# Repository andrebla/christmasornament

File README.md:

# Christmas ornament

Christmas tree ornament for 2020 JLCPCB Design Challenge based in christmas PNG Designed By Co illustrasi from <a href="https://pngtree.com/">Pngtree.com</a>

It is a simple ornament using less than ten components, listed above:
## Bill of Materials ##
| # | Qty | Description |
| - | --- | :---------- | 
| 1 | 3 | 5mm red LED |
| 2 | 3 | 220 ohm 0603 resistor |
| 3 | 1 | smd 12mm battery holder |
| 4 | 1 | cr1220 battery |

It's simple and easy to build!

For more informaion about PCB fabrication visit JLCPCB - <a href="https://jlcpcb.com/">jlcpcb.com</a>

## 3D Render ##
|  | 
| - |

|  |
| - |

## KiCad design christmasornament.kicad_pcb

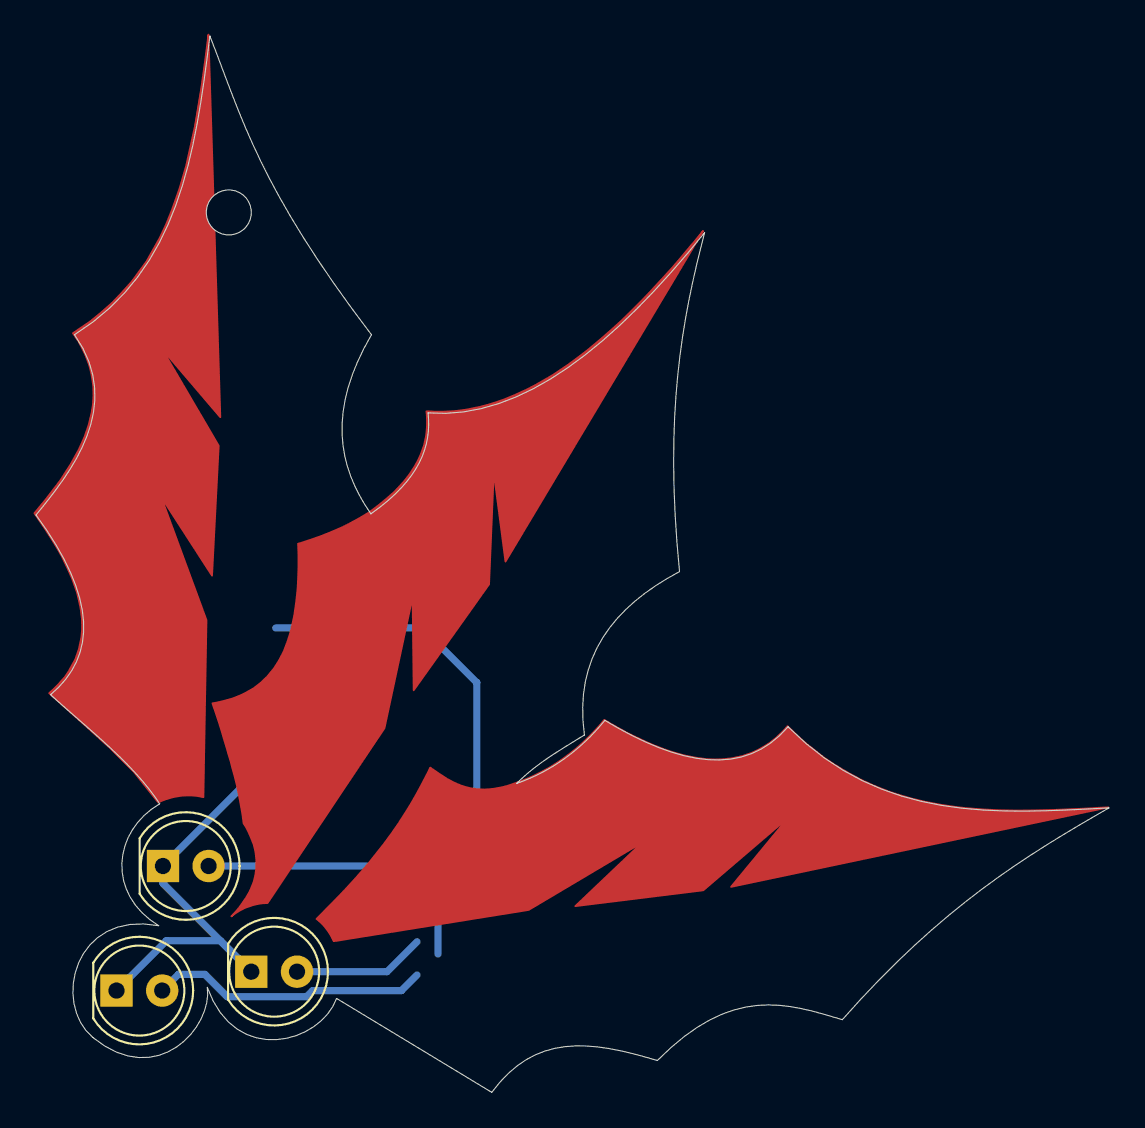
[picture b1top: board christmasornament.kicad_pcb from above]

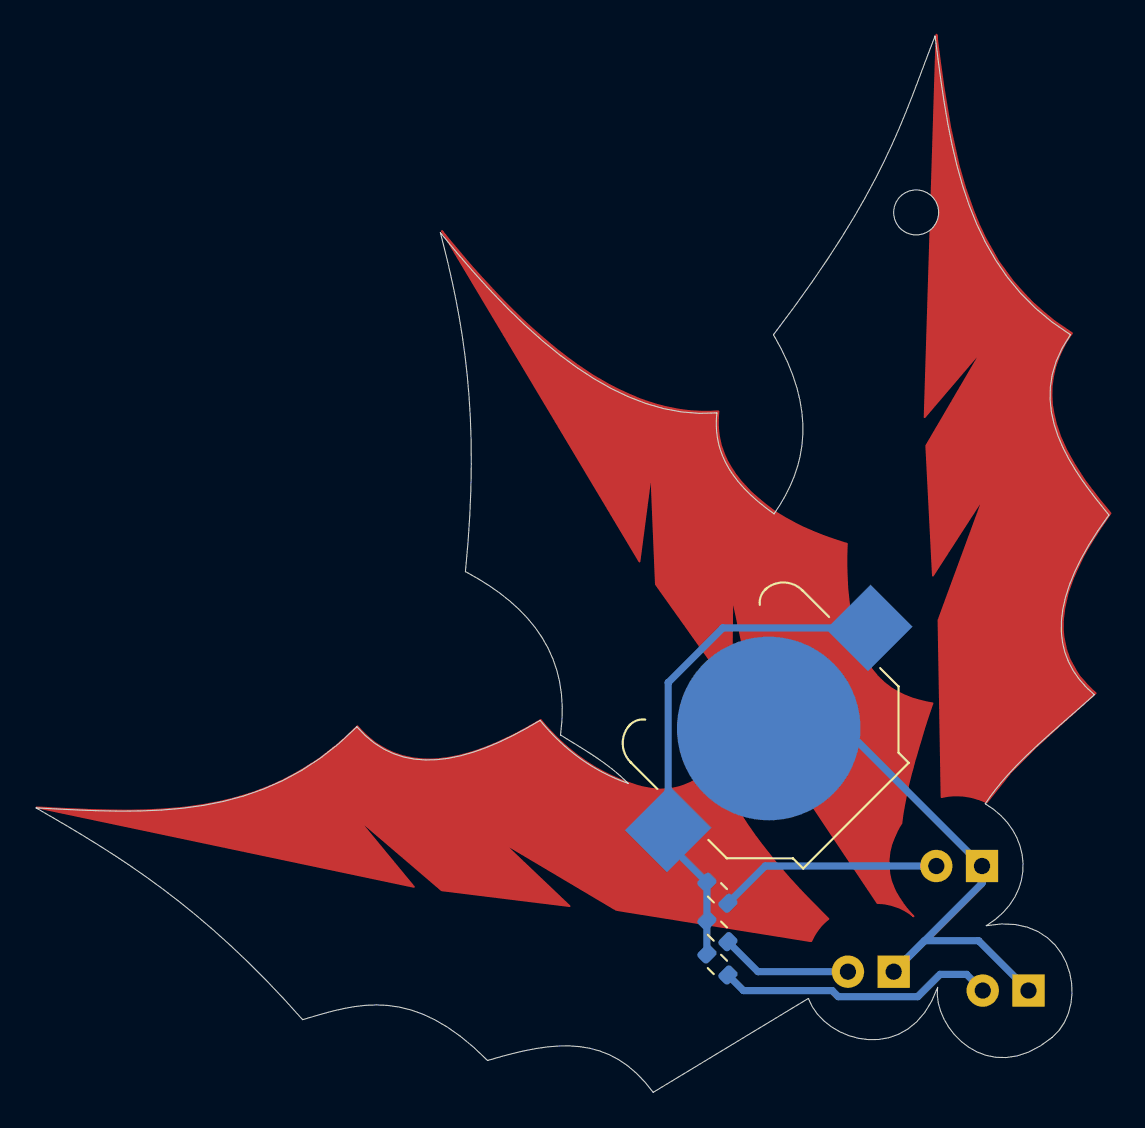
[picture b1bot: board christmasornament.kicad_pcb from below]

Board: 2 copper layers, 59.6 x 58.7 mm, 8 parts (4 on the bottom side), 5 nets.

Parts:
BT1: Battery_Cell; BatteryHolder_Keystone_3000_1x12mm
D1, D2, D3: LED; LED_D5.0mm
H1: MountingHole; MountingHole_2.5mm
R1, R2, R3: 220R; R_0603_1608Metric

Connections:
GND: BT1.2, D1.1, D2.1, D3.1
unnamed: D1.2, R1.1
unnamed: D2.2, R2.1
unnamed: D3.2, R3.1
VCC: BT1.1, R1.2, R2.2, R3.2
